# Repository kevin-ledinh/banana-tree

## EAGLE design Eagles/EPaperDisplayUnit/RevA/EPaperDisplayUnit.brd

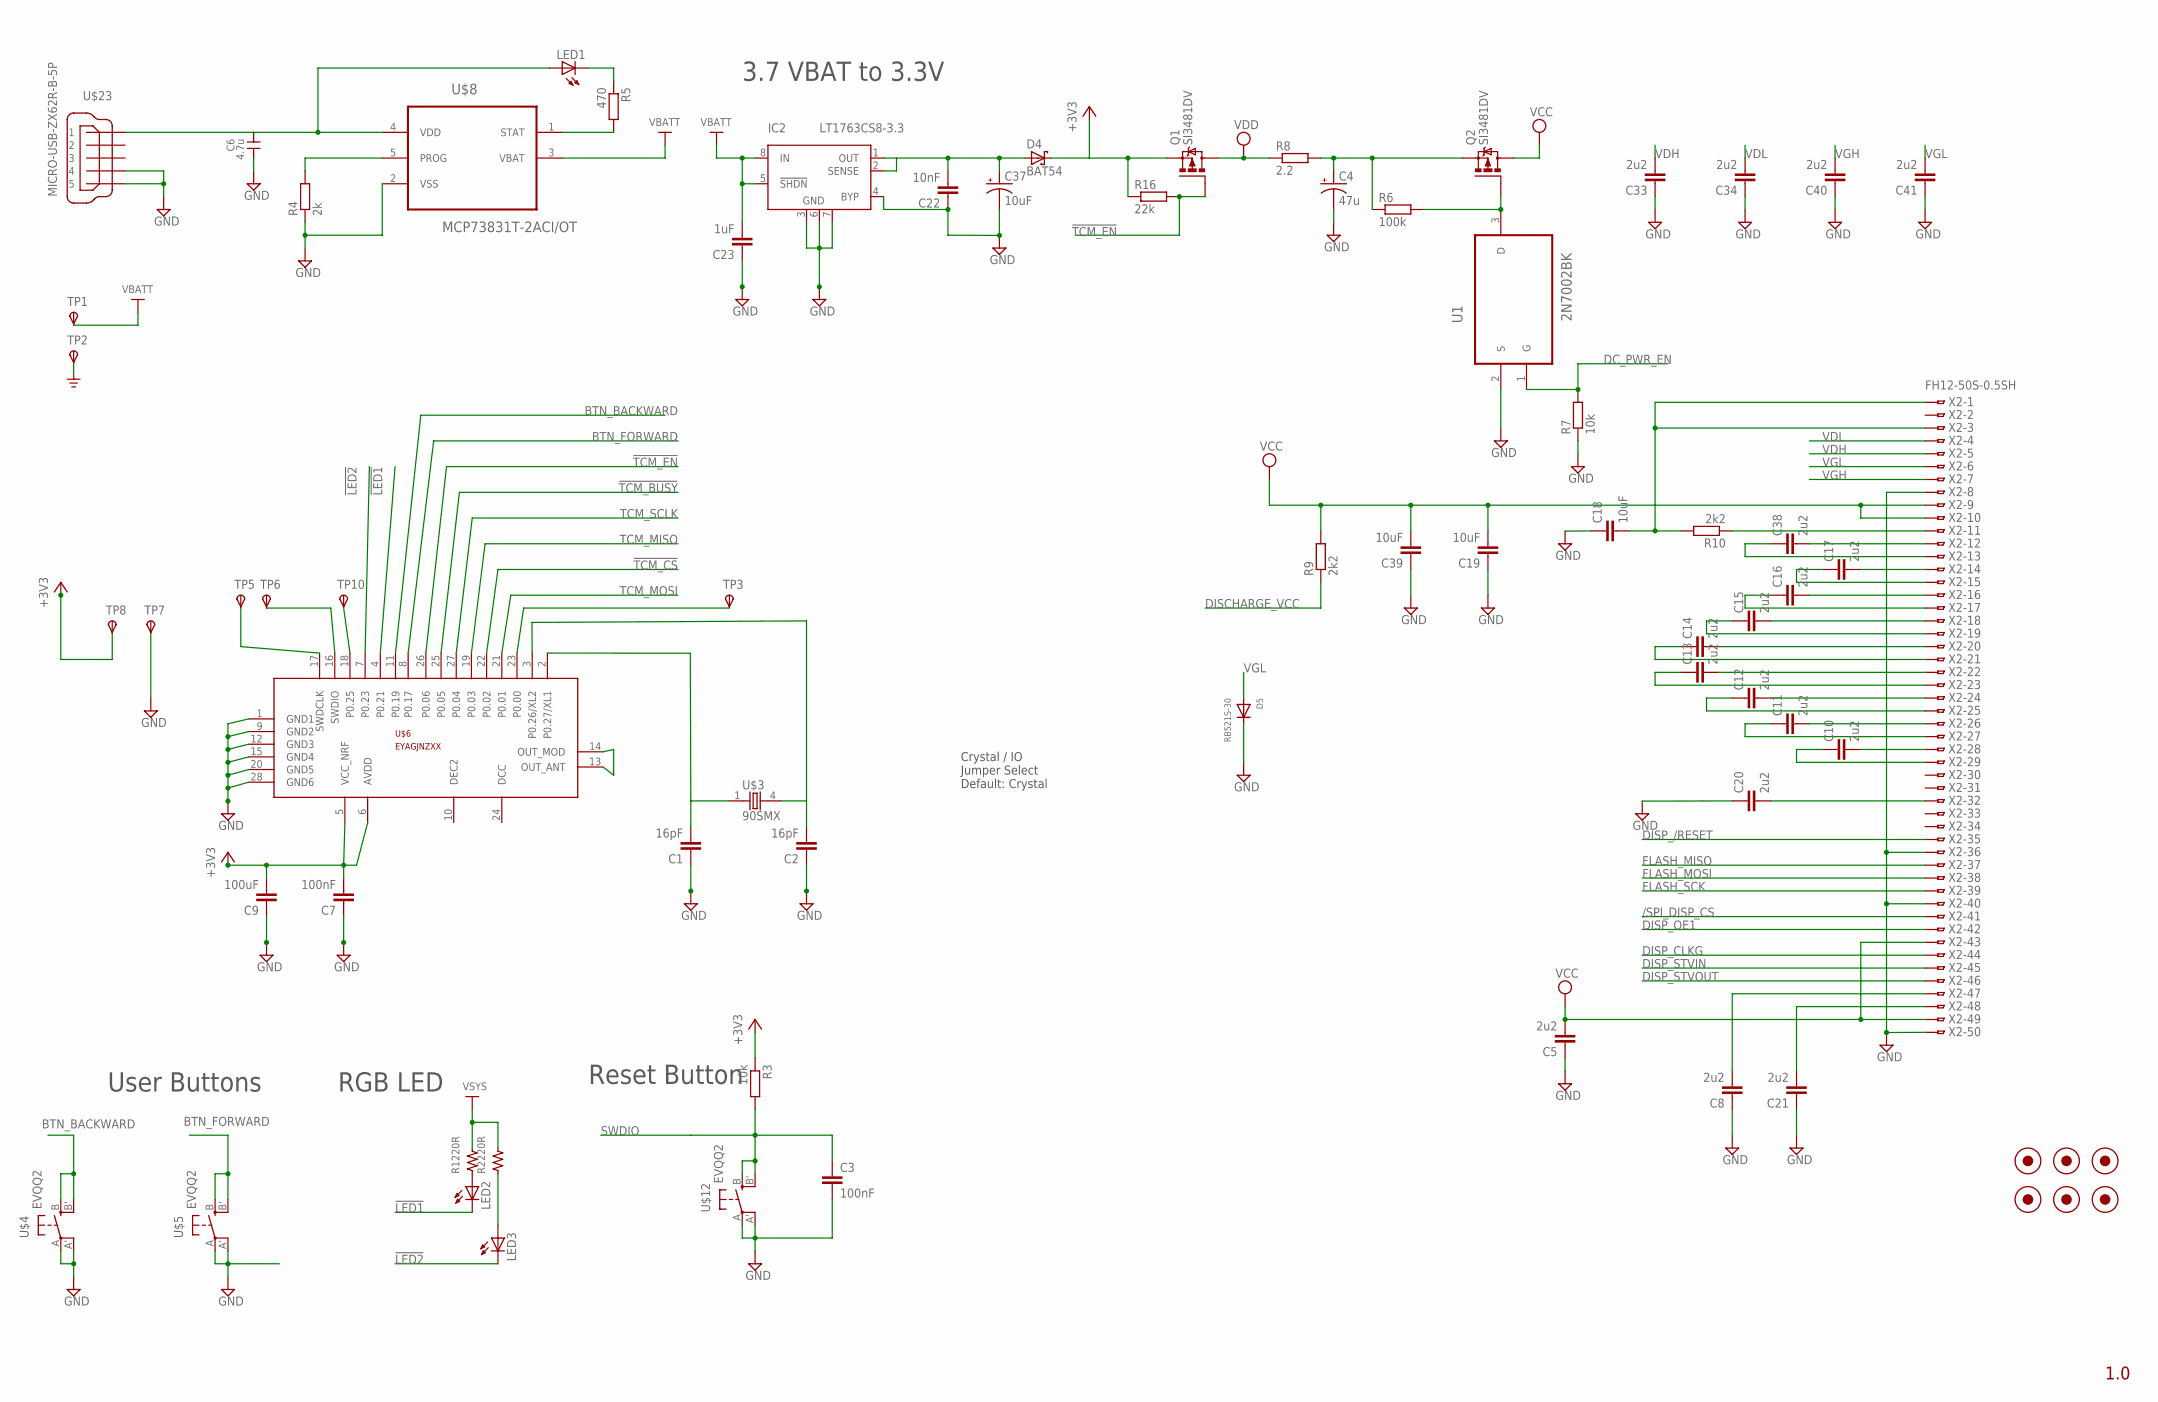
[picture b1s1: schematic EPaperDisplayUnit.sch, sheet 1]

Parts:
C1, C2: 16pF; C0402
C3: 100nF; C0603
C4: 47u; B/3528-21R
C5, C8, C10, C11, C12, C13, C14, C15, C16, C17, C20, C21, C33, C34, C38, C40, C41: 2u2; C0402
C6: 4.7u; SMD0603
C7: 100nF; C0402
C9: 100uF; C0402
C18, C19, C39: 10uF; C0402
C22: 10nF; C0402
C23: 1uF; C0402
C37: 10uF; 085CS_1AR
D4: BAT54; SOT23
D5: RB521S-30; SOD-523
FID1, FID2, FID3, FID4, FID5, FID6: FIDUCIAL-.04
IC2: LT1763CS8-3.3; SOIC8
LED1: LEDCHIPLED_0603; CHIPLED_0603
LED2, LED3: LEDCHIP-LED0603; CHIP-LED0603
Q1, Q2: SI3481DV; TSOP-6.PAC
R1, R2: 220R; SMD0402
R3, R7: 10k; R0402
R4: 2k; R0402
R5: 470; R0402
R6: 100k; R0402
R8: 2.2; R0402
R9, R10: 2k2; R0402
R16: 22k; R0402
TP1, TP2, TP3, TP5, TP6, TP7, TP8, TP10: TPSPAD1-13Y; P1-13Y
U1: 2N7002BK; SOT95P230X110-3N
U$3: 90SMX; 9XSMX
U$4, U$5, U$12: EVQQ2; EVQ-Q2
U$6: EYAGJNZXXEYAGJNZXX; EYAGJNZXX
U$8: MCP73831T-2ACI/OT; SOT95P280X145-5N
U$23: MICRO-USB-ZX62R-B-5P; ZX62R-B-5P
X2: FH12-50S-0.5SH

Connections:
!LED1: LED2.C, U$6.4 (P0.21)
!LED2: LED3.C, U$6.7 (P0.23)
!TCM_BUSY: U$6.25 (P0.05); also elsewhere on the board
!TCM_CS: U$6.22 (P0.02); also elsewhere on the board
!TCM_EN: Q1.3 (G), R16.2, U$6.26 (P0.06)
+3V3: C7.2, C9.2, D4.3 (C), Q1.4 (S), R3.1, R16.1, TP8.TP, U$6.5 (VCC_NRF), U$6.6 (AVDD)
/SPI_DISP_CS: X2.41; also elsewhere on the board
BTN_BACKWARD: U$4.B (S), U$4.B' (S1), U$6.11 (P0.19)
BTN_FORWARD: U$5.B (S), U$5.B' (S1), U$6.8 (P0.17)
DC_PWR_EN: R7.2, U1.1 (G); also elsewhere on the board
DISCHARGE_VCC: R9.1; also elsewhere on the board
DISP_/RESET: X2.35; also elsewhere on the board
DISP_CLKG: X2.44; also elsewhere on the board
DISP_OE1: X2.42; also elsewhere on the board
DISP_STVIN: X2.45; also elsewhere on the board
DISP_STVOUT: X2.46; also elsewhere on the board
FLASH_MISO: X2.37; also elsewhere on the board
FLASH_MOSI: X2.38; also elsewhere on the board
FLASH_SCK: X2.39; also elsewhere on the board
GND: C1.1, C2.1, C3.2, C4.-, C5.1, C6.2 (3), C7.1, C8.1, C9.1, C18.1, C19.1, C20.1, C21.1, C22.1, C23.1, C33.1, C34.1, C37.-, C39.1, C40.1, C41.1, D5.K (C), IC2.3 (GND), IC2.4 (BYP), IC2.6 (GND), IC2.7 (GND), R4.1, R7.1, TP2.TP, TP7.TP, U$4.A, U$4.A' (P1), U$5.A, U$5.A' (P1), U$6.1 (GND1), U$6.9 (GND2), U$6.12 (GND3), U$6.15 (GND4), U$6.20 (GND5), U$6.28 (GND6), U$8.2 (VSS), U$12.A, U$12.A' (P1), U$23.4, U$23.5, X2.8, X2.36, X2.40, X2.50; also elsewhere on the board
unnamed: TP10.TP, U$6.18 (P0.25)
unnamed: C6.1, LED1.A, U$8.4 (VDD), U$23.1
unnamed: C22.2, C37.+, D4.1 (A), IC2.1 (OUT), IC2.2 (SENSE)
unnamed: R4.2, U$8.5 (PROG)
unnamed: LED1.C, R5.1
unnamed: C20.2, X2.32
unnamed: R5.2, U$8.1 (STAT)
unnamed: Q2.3 (G), R6.2, U1.3 (D)
unnamed: C4.+, Q2.4 (S), R6.1, R8.2
unnamed: C10.1, X2.29
unnamed: C10.2, X2.28
unnamed: C11.1, X2.27
unnamed: C11.2, X2.26
unnamed: C12.1, X2.25
unnamed: C12.2, X2.24
unnamed: C2.2, U$3.4 (2), U$6.3 (P0.26/XL2)
unnamed: C1.2, U$3.1, U$6.2 (P0.27/XL1)
unnamed: C13.1, X2.23
unnamed: C13.2, X2.22
unnamed: C14.1, X2.21
unnamed: C14.2, X2.20
unnamed: C15.1, X2.19
unnamed: C16.1, X2.17
unnamed: C16.2, X2.16
unnamed: C17.1, X2.15
unnamed: C17.2, X2.14
unnamed: C38.1, X2.13
unnamed: C38.2, X2.12
unnamed: LED2.A, R1.1
unnamed: LED3.A, R2.1
unnamed: C18.2, R10.2, X2.1, X2.3
unnamed: R10.1, X2.11
unnamed: TP3.TP, U$6.23 (P0.00)
unnamed: C15.2, X2.18
unnamed: U$6.13 (OUT_ANT), U$6.14 (OUT_MOD)
SWCLK: TP5.TP, U$6.17 (SWDCLK)
SWDIO: C3.1, R3.2, TP6.TP, U$6.16 (SWDIO), U$12.B (S), U$12.B' (S1)
TCM_MISO: U$6.19 (P0.03); also elsewhere on the board
TCM_MOSI: U$6.21 (P0.01); also elsewhere on the board
TCM_SCLK: U$6.27 (P0.04); also elsewhere on the board
VBATT: C23.2, IC2.5 (!SHDN), IC2.8 (IN), TP1.TP, U$8.3 (VBAT)
VCC: C5.2, C19.2, C39.2, Q2.1 (D), Q2.2 (D), Q2.5 (D), Q2.6 (D), R9.2, X2.9, X2.10, X2.43, X2.49
VDD: Q1.1 (D), Q1.2 (D), Q1.5 (D), Q1.6 (D), R8.1; also elsewhere on the board
VDH: C33.2, X2.5
VDL: C34.2, X2.4
VGH: C21.2, C40.2, X2.7, X2.48
VGL: C8.2, C41.2, D5.A, X2.6, X2.47
VSYS: R1.2, R2.2

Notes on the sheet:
1.0
Crystal / IO Jumper Select Default: Crystal
3.7 VBAT to 3.3V
RGB LED
User Buttons
Reset Button

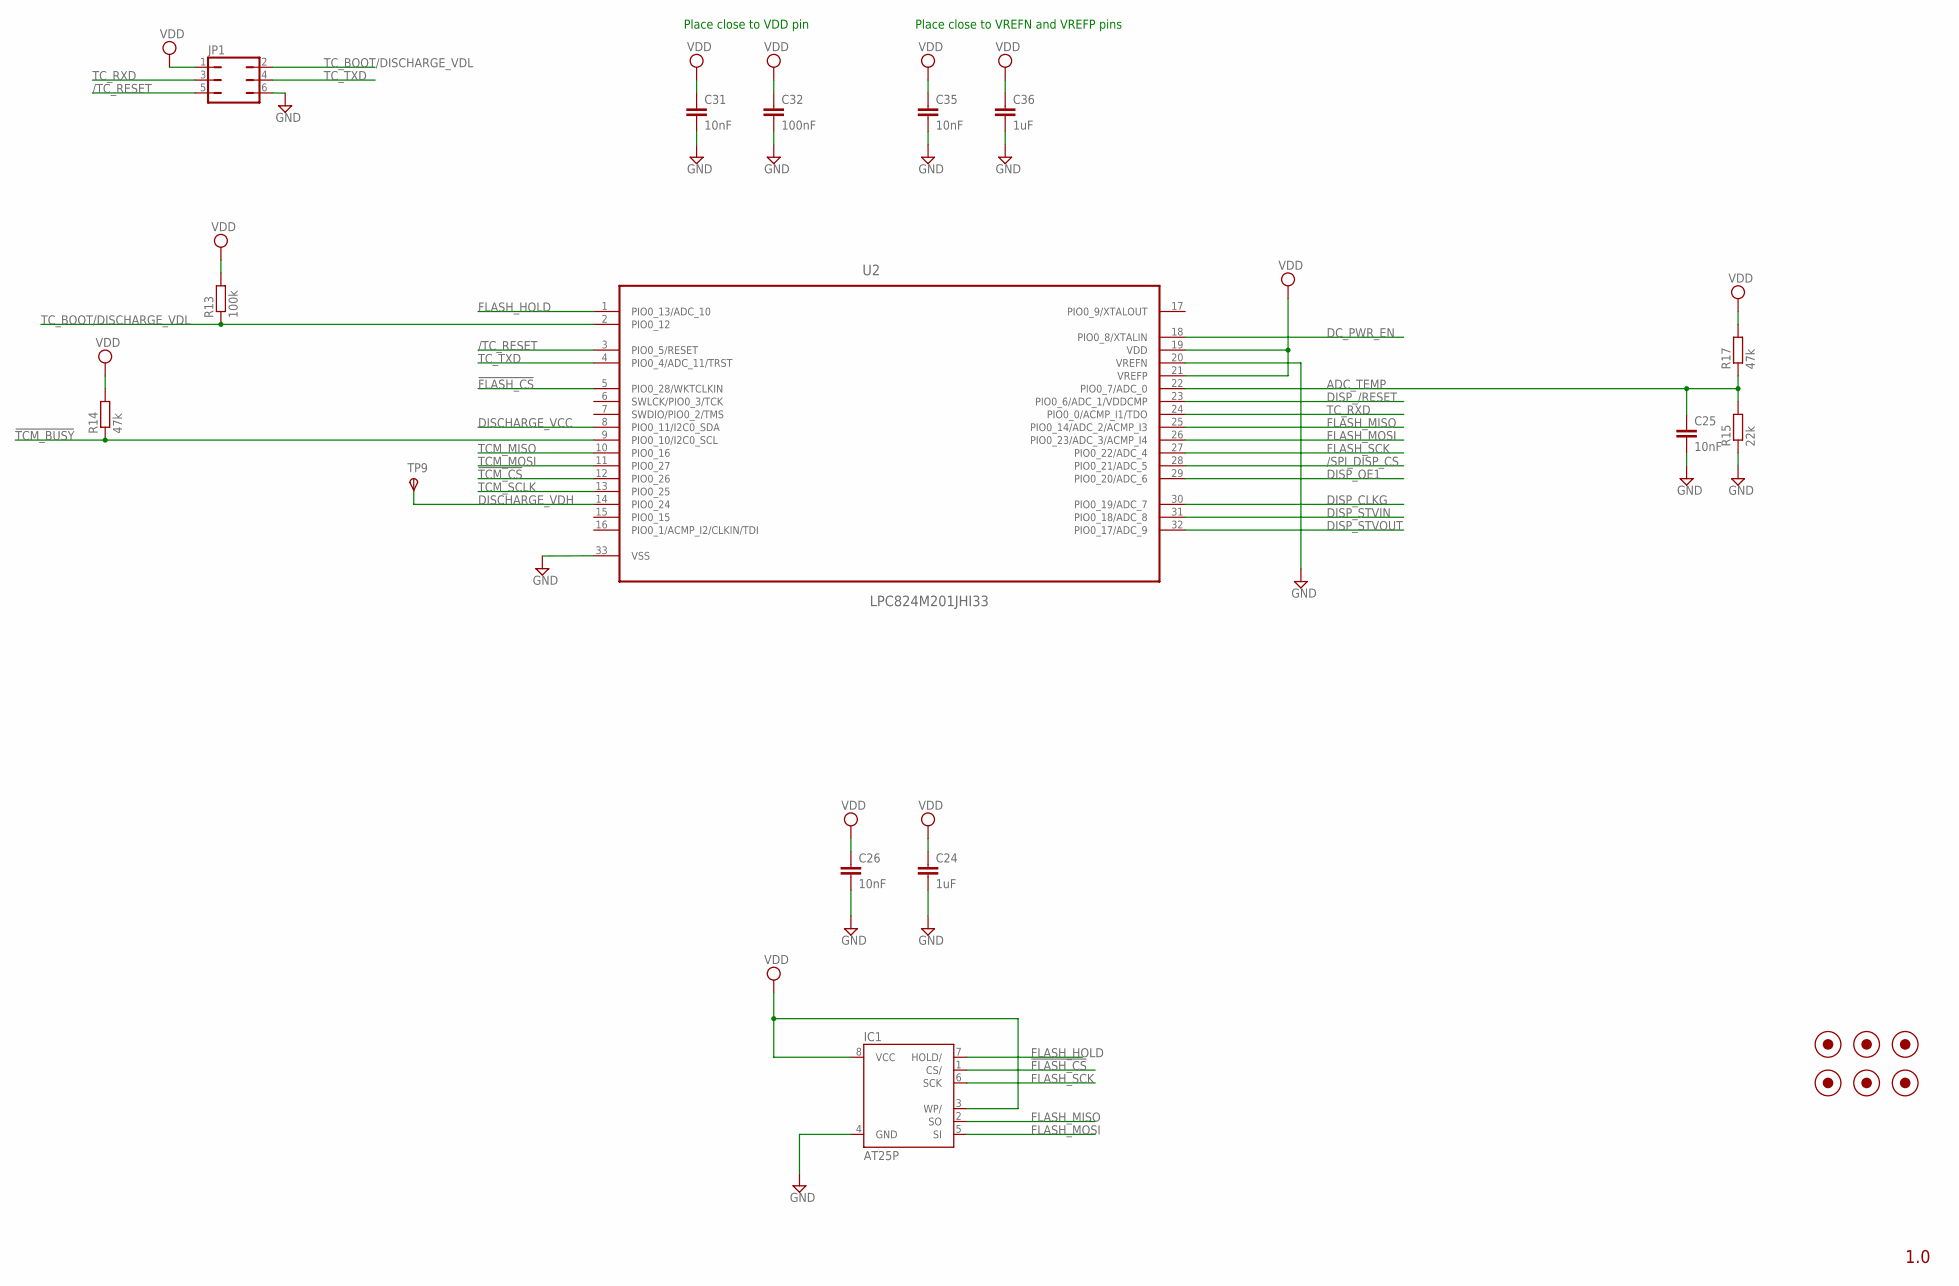
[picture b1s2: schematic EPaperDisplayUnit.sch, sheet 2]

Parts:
C24, C36: 1uF; C0402
C25, C26, C31, C35: 10nF; C0402
C32: 100nF; C0402
FID7, FID8, FID9, FID10, FID11, FID12: FIDUCIAL-.04
IC1: AT25P; DIL08
JP1: JP3Q
R13: 100k; R0402
R14, R17: 47k; R0402
R15: 22k; R0402
TP9: TPSPAD1-13Y; P1-13Y
U2: LPC824M201JHI33; QFN65P700X700X100-33N

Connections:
!FLASH_CS: IC1.1 (CS/), U2.5 (PIO0_28/WKTCLKIN)
!TCM_BUSY: R14.1, U2.9 (PIO0_10/I2C0_SCL); also elsewhere on the board
!TCM_CS: U2.12 (PIO0_26); also elsewhere on the board
/SPI_DISP_CS: U2.28 (PIO0_21/ADC_5); also elsewhere on the board
/TC_RESET: JP1.5, U2.3 (PIO0_5/RESET)
ADC_TEMP: C25.1, R15.2, R17.1, U2.22 (PIO0_7/ADC_0)
DC_PWR_EN: U2.18 (PIO0_8/XTALIN); also elsewhere on the board
DISCHARGE_VCC: U2.8 (PIO0_11/I2C0_SDA); also elsewhere on the board
DISCHARGE_VDH: TP9.TP, U2.14 (PIO0_24)
DISP_/RESET: U2.23 (PIO0_6/ADC_1/VDDCMP); also elsewhere on the board
DISP_CLKG: U2.30 (PIO0_19/ADC_7); also elsewhere on the board
DISP_OE1: U2.29 (PIO0_20/ADC_6); also elsewhere on the board
DISP_STVIN: U2.31 (PIO0_18/ADC_8); also elsewhere on the board
DISP_STVOUT: U2.32 (PIO0_17/ADC_9); also elsewhere on the board
FLASH_HOLD: IC1.7 (HOLD/), U2.1 (PIO0_13/ADC_10)
FLASH_MISO: IC1.2 (SO), U2.25 (PIO0_14/ADC_2/ACMP_I3); also elsewhere on the board
FLASH_MOSI: IC1.5 (SI), U2.26 (PIO0_23/ADC_3/ACMP_I4); also elsewhere on the board
FLASH_SCK: IC1.6 (SCK), U2.27 (PIO0_22/ADC_4); also elsewhere on the board
GND: C24.2, C25.2, C26.2, C31.2, C32.2, C35.2, C36.2, IC1.4 (GND), JP1.6, R15.1, U2.20 (VREFN), U2.33 (VSS); also elsewhere on the board
TCM_MISO: U2.10 (PIO0_16); also elsewhere on the board
TCM_MOSI: U2.11 (PIO0_27); also elsewhere on the board
TCM_SCLK: U2.13 (PIO0_25); also elsewhere on the board
TC_BOOT/DISCHARGE_VDL: JP1.2, R13.1, U2.2 (PIO0_12)
TC_RXD: JP1.3, U2.24 (PIO0_0/ACMP_I1/TDO)
TC_TXD: JP1.4, U2.4 (PIO0_4/ADC_11/TRST)
VDD: C24.1, C26.1, C31.1, C32.1, C35.1, C36.1, IC1.3 (WP/), IC1.8 (VCC), JP1.1, R13.2, R14.2, R17.2, U2.19 (VDD), U2.21 (VREFP); also elsewhere on the board

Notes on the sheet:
1.0
Place close to VDD pin
Place close to VREFN and VREFP pins

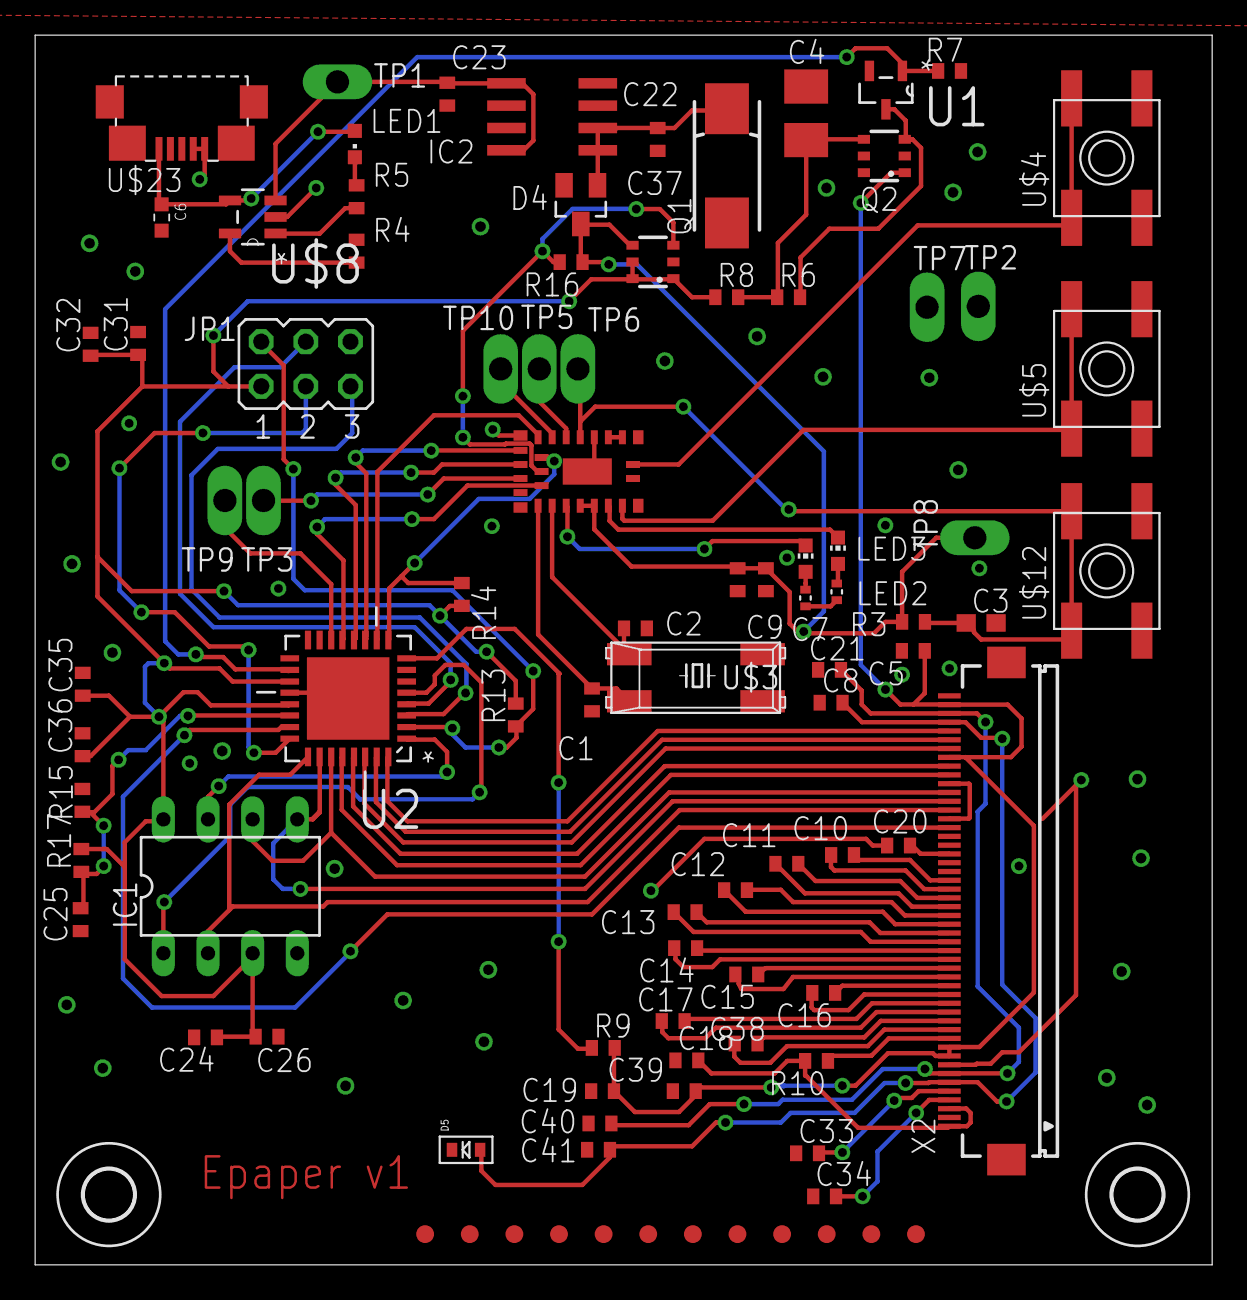
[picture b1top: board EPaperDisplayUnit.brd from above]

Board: 2 copper layers, 67.0 x 70.0 mm, 95 parts (0 on the bottom side), 76 nets.

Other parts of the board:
U$2, U$9: 2,8

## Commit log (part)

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2015-11-13 committing finance and info folder
2015-11-13 Committing system requirements
2015-11-13 update design defnition for prototypong system.
    TODO: write a plan for development.
    Recommended to phases: prototyping on dev boards and prototyping to standalone PCB.
2015-11-13 committing CDC-UART KDS project. Added USB CDC and uart PE component.
2015-11-14 committing codewarrior project. Compiled ok
2015-11-14 committing kds project. Compiled ok. Choose KDS because unlimited code size for kinetis
2015-11-14 add info for the FRDM-KL25Z BOARD
2015-11-14 USB CDC project works
2015-11-18 add Bluetooth dev kit order
    add Bluetooth dev kit order
2015-11-21 update Design requirements.docx
    rename Design definition.docx to E-paper-display-unit-Design-definition.docx
2015-11-21 create docs folder.
    Move req doc and display unit design def
2015-11-21 rename Design requirements.docx to E-paper-Display-System-Requirements.docx
2015-11-21 committing skeleton version of E-paper-Display-Unit-Android-Interface-Definition.docx
2015-11-29 committing nordic reference document
2015-12-02 committing tools from Pervasive and waveshare
2015-12-05 test commit
2015-12-06 comitting datasheet for Waveshare epaper.
2015-12-06 re-upload datasheet for Waveshare board.
2015-12-06 committing Pervasive Digi Key order.
2015-12-14 committing main tools used in the project.
    nRF51 SDK 9.0
2015-12-14 committing main tools used in the project.
    nRF51 SDK 10.0
    SDK 10.0 packs
    SDK 9.0 packs
2015-12-15 committing minute of the call to MPico sys.
2015-12-15 committing E-paper-display-unit-Design-definition.docx * add pricing
2015-12-16 TC2-P441-231_v1.1_designGuide_rA.pdf
2015-12-16 designer guide
2015-12-28 committing nRF SDK 10.0
    NOTE: there is SDK 11.0
2015-12-28 Add timing controller without any SPI references
2015-12-28 committing skeleton file for TCM GPIO driver: /ENABLE and /BUSY
2015-12-28 committing GPIO code with enable and busy signal coded. Compiled ok but not tested.
    Proceed to port SPI code into a separate file
2015-12-28 proceed to connect the TCM board with bLE board. COmpiled ok
2015-12-29 minimise delay between consecutive SPI commands down to 1ms
2015-12-29 committing binary files.
2016-01-02 committing image conversion tool for Pervasive display
2016-01-02 committing java code snippet for Pervasive conversion tool
2016-01-02 committing nRF UART android app project.
2016-01-04 transfer file ok from phone to the BLE board and back through UART.
    Ready to be transferred to the EPD
2016-01-04 committing preliminary TCM driver to BLE Uart project.
2016-01-04 committing code that can read TCM device info.
    TODO: transfer picture
2016-01-09 [see #1]-(SW--Port KL25 code to nRF51)
    committing sample2.epd to switch between 2 different pictures for testing.
2016-01-09 [see #1]-(SW--Port KL25 code to nRF51)
    UART app is able to display alternative sample pictures.
2016-01-09 [see #1]-(SW--Port KL25 code to nRF51)
    Bluetooth dev board is capable of displaying pictures sent from the UART app.
2016-01-09 [see #1]-(SW--Port KL25 code to nRF51)
    created a simple protocol for sending image over to EPD via BLE board.
2016-01-14 [see #3]--(SW--Increase data rate to the EPD)
    time elapse to transfer is now about 2 seconds. Parameters need to be investigated:
    * number of connection events within a connection interval
    * Can more bytes be sent?
2016-01-16 [see #3]--(SW--Increase data rate to the EPD)
    use onWriteCharacteristic callback to check for complete tx. Works reliably.
    Have not try requesting MTU size.
    It is a good time to start on ebook side.
2016-01-16 [see #3]--(SW--Increase data rate to the EPD)
    an image tx session has to be always followed by a finish command to ensure that the BLE board to back to wait for cmd state.
2016-01-16 [see #3]--(SW--Increase data rate to the EPD)
    The data rate is acceptable for now.
    Move on to buttons.
2016-01-16 [see #4]--(SW--Set up GPIO port on the BLE board to send page turning command)
    GPIO interrupt is now set up. Some debouncing to be sorted out
2016-01-16 [see #4]--(SW--Set up GPIO port on the BLE board to send page turning command)
    backwards and forward command can be seen on the Android side.
2016-01-16 [see #4]--(SW--Set up GPIO port on the BLE board to send page turning command)
    button press initiate img tx ok.
    However the tx transferred is offset.
2016-01-16 [see #4]--(SW--Set up GPIO port on the BLE board to send page turning command)
    button press initiate img tx ok.
    However the tx transferred is offset. Looks like the img is missing ...
2016-01-19 SW--Investigate missing data chunk on the BLE board #7
    add a small delay after sending Img command. Seems to be working ok. No missing img data yet.
2016-01-28 readme.txt
2016-02-20 SW--Investigate missing data chunk on the BLE board #7
    Committing BLE code. Closing ticket.
2016-02-20 [Look for modules that uses Nordic SoC #2]
    committing design files for the BMD-200 module
2016-02-20 [Draw schematic for the display unit #8]
    committing draft schematic for the display unit.
    Only has part of the BLE unit.
2016-02-21 [HW--Select suitable USB charge IC #9] committing charger IC datasheet
2016-02-21 [Draw schematic for the display unit #8]
    add power circuit to schematic.
    TODO:
    * connect peripheral to BLE module
    * ask Nhan T to draw the E-paper display part
2016-02-28 display unit - schem1
2016-02-28 recommiting files
2016-03-06 [Draw schematic for the display unit #8]
    copied every epaper display schematic into the main Eagle project.
2016-03-06 Schematic libraries committing Signed-off-by: tcnhan2512 <tcnhan2512@gmail.com>
2016-03-06 schematic lib committing Signed-off-by: tcnhan2512 <tcnhan2512@gmail.com>
2016-03-06 lib committing Signed-off-by: tcnhan2512 <tcnhan2512@gmail.com>
2016-03-06 [Draw schematic for the display unit #8]
    Fix errors in the current schematic
2016-03-07 [Draw schematic for the display unit #8]
    cleaning up schematic and add signal to the BLE module.
    add pin assignment spreadsheet.
2016-03-19 [Draw schematic for the display unit #8]
    Add BMD-200.lbr to repo, and use it in the schematic
    At this point I don't think we want to do LGA package just yet. It will give us more pain than good.
2016-03-19 [Draw schematic for the display unit #8]
    clean up the schematic. Ready for another review before PCB layout
2016-03-19 [Draw schematic for the display unit #8]
    create a folder for additional libraries
2016-03-19 [Draw schematic for the display unit #8]
    Add a hirose USB connector for charging
2016-03-19 [Draw schematic for the display unit #8]
    Move schematic to Rev A folder
2016-03-19 [Draw schematic for the display unit #8]
    Delete schematic because it is in the top folder.
    It has been move into Rev A folder.
2016-03-19 [Draw schematic for the display unit #8]
    add N5150M8CD library. Ready to change schematic
2016-03-19 [Draw schematic for the display unit #8]
    committing pin assignment for N5150M8CD
2016-03-19 [Draw schematic for the display unit #8]
    committing Eagle library file for EYAGJNZXX
2016-03-20 [Draw schematic for the display unit #8]
    use inch for Eagle ... don't like it but for fast turn round it needs to be done
2016-03-20 [Draw schematic for the display unit #8]
    committing final version of Rev A.
    Need to visit the BOM later on.
    Ok to proceed with PCB layout
2016-03-20 [Draw schematic for the display unit #8]
    minor changes to Rev A
2016-03-20 [Draw schematic for the display unit #8]
    fix a full up res value
2016-03-20 [Draw schematic for the display unit #8]
    change resistors and caps to 0402 package to save space on the upcoming PCB
2016-04-26 Board design committing
2016-04-30 committing java code from picosys. Some syntax errors to be fixed.
2016-04-30 restructure source file.
2016-04-30 committing Conversion tool and sample image.
2016-04-30 code is compiled and run but the output size is too big.
    Precisely 50 times bigger than need be(!?)
    Clearly a bug somewhere.
2016-04-30 Conversion code create a valid epd file. Next step is to create some book pages.
2016-04-30 create a picture with Sample Text ok.
2016-04-30 sample image ok. Now need to rotate the image 90 degree
2016-04-30 rotate book page right left ok.
2016-04-30 yup, I was right. Somebody already did wrapping string.
    Display ok. Clean up the code later.
    Need to specify how many lines it can display stuff.
2016-04-30 using Times New Roman for now. With the string wrapping function, no matter what the Font is, text can be display.
    TODO: REFACTOR. This code is messsssyyyyyyyyy
2016-05-05 committing skeleton android proj
2016-05-05 add sample image
2016-05-05 rename image
2016-06-29 committing compile file conversion code.
    Ready to test the transfer test.
2016-07-03 convert picture ok. Now to convert some texts.
2016-07-03 generate text ok. Now need to convert a book page.
2016-07-06 convert long text into a picture ok.
    Now need to get a proper ebook reader and integrate with the bluetooth app.
2016-11-01 Android--sw--Get an EPUB reader app and evaluate #13
    Get content from web view ok.
    The content tends to be a whole chapter.
2016-11-02 Android--SW--Integrate .epd file generator #14
    Add two dummy class as the top level for EPD and BLE services.
    add three buttons for Prev, Display Top, and Fwd.
    Code compiled ok. Now to set up broadcast service between the book view and EPD service.
2017-01-22 Android--SW--Integrate .epd file generator #14
    Scanning BLE ok, now to connect auto
2017-01-22 Android--SW--Integrate .epd file generator #14
    committing UART service from BLE example code
2017-01-22 Android--SW--Integrate .epd file generator #14
    add service handlers (broadcast service). Compiled ok but need to add sample pics and test.
2017-02-05 Android--SW--Integrate .epd file generator #14
    integrated EPD file generator into ebook.
    Compiled ok. Not yet tested.
2017-02-12 Android--SW--Integrate .epd file generator #14
    Use and index to go back and forth on a chapter.
2017-02-12 Android--SW--Integrate .epd file generator #14
    use indx and array list ok.
    TODO:
    * app freezes if BLE device disconnects
    * investigate a way to send noti to do book action: next chapter, auto display new chapter.
2017-02-18 #6 Need to test the following functions: At the beginning of a chapter, pressing BACK will do nothing; press FORWARD will display the next part of the chapter At the end of a chapter, pressing BACK w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
    Committing code. Compiled ok but need testing.
2017-02-18 #6
    Add more actions as per description in the previous commit.
    Need testing.
2017-02-19 #6
    At the beginning of a chapter, pressing BACK will do nothing; press FORWARD will display the next part of the chapter
    -- DONE, tested.
    When a book is loaded, the first part of the chapter will be transmitted.
    -- DONE, tested
    At the end of a chapter, pressing BACK will display the previous part of the chapter; pressing FORWARD will display the next chapter.
    -- TODO
2017-02-19 #6
    At the end of a chapter, pressing BACK will display the previous part of the chapter;
    --DONE tested.
    pressing FORWARD will display the next chapter.
    -- DONE tested.
2017-02-25 #18
    If multiple request as received, the next chapter chunk will not be prepared until the "RX: MSG_TYPE_ACK Rx: no error" msg is received, only the chunk index is incremented.
    -- DONE. Not tested yet
    If the index reach the two extremes of a chapter, it will stick there without going to the next chapter.
    -- Change this a bit. No need for the sticking point. Just go to the adjacent chapter.
2017-02-25 #18
    Change signal into a more meaningful name.

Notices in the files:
parts and their libraries:
frames: Copyright 2014 Rigado, LLC
